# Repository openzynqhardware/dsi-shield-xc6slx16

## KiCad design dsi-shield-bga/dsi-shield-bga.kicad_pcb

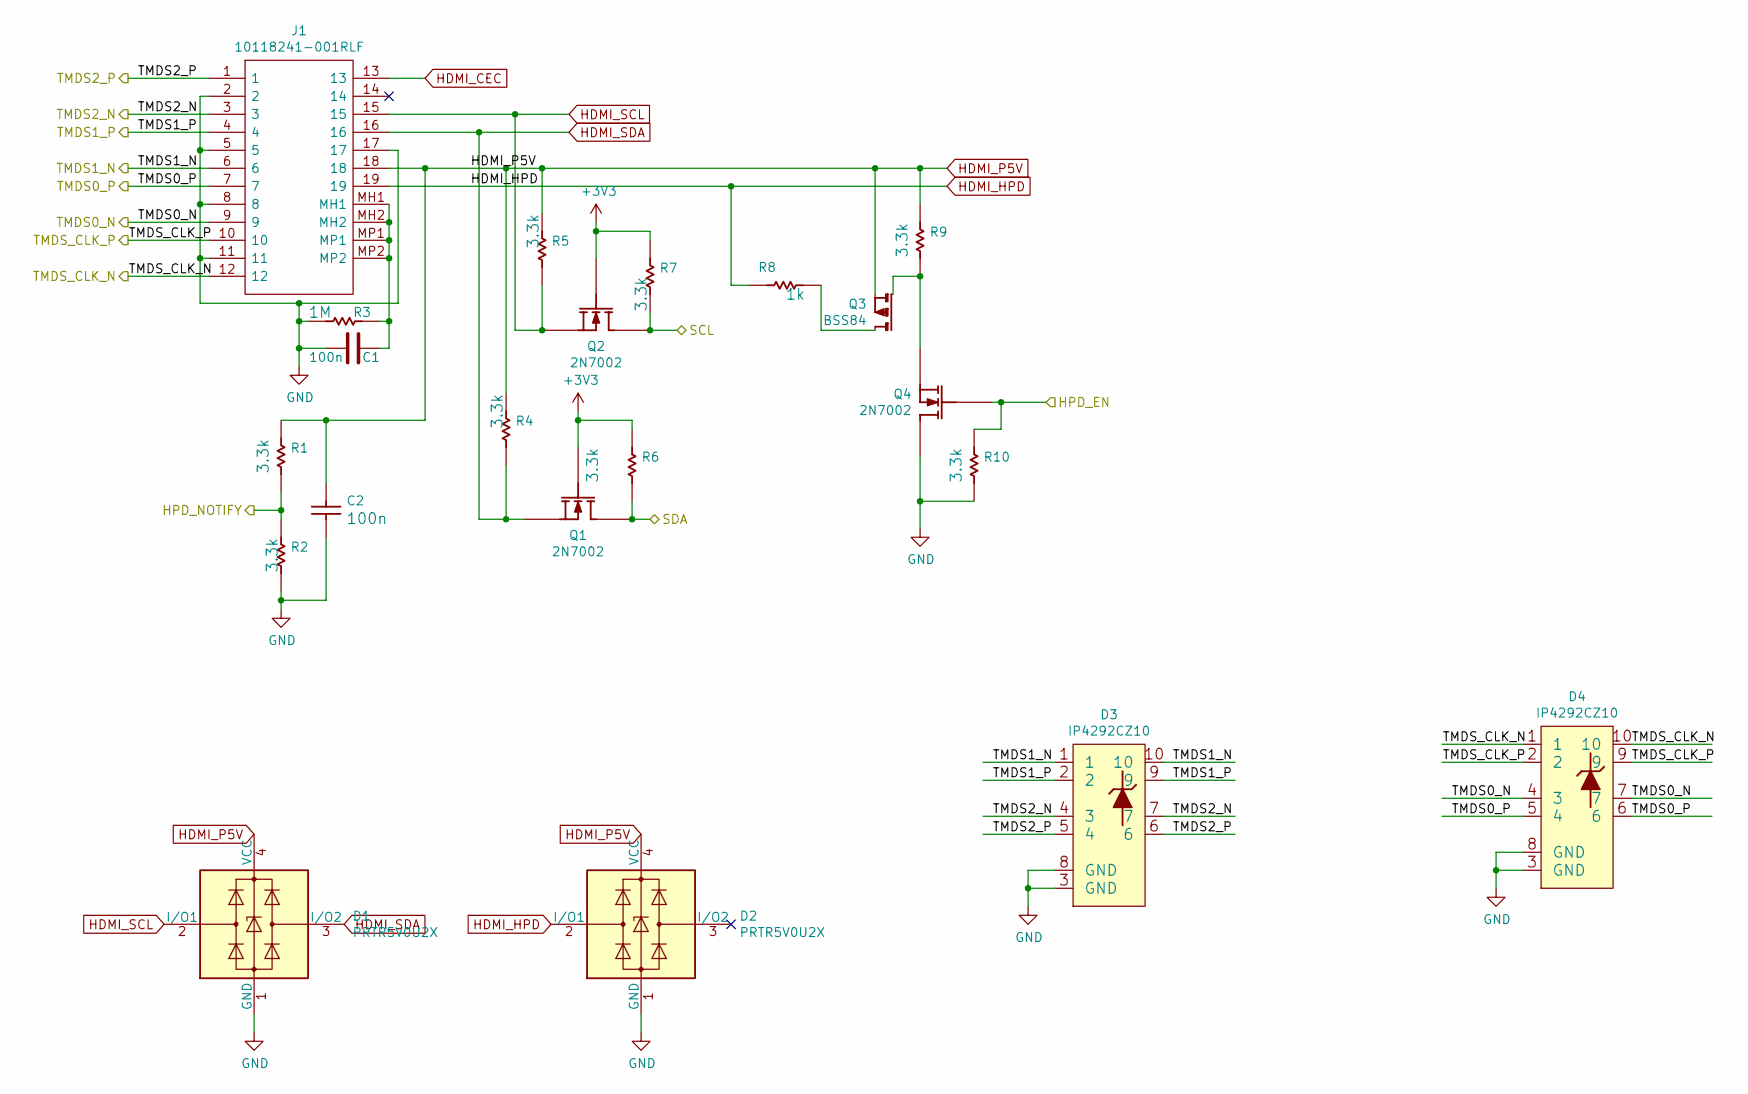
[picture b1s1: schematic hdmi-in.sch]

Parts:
C1, C2: 100n; C_01005_0402Metric
D1, D2: PRTR5V0U2X; SOT-143
D3, D4: IP4292CZ10; SOT1176-1
J1: 10118241-001RLF; 10118241001RLF; Mouser Part Number 649-10118241-001RLF
Q1, Q2, Q4: 2N7002; SOT-23
Q3: Q_BSS84; SOT-23
R1, R2, R4, R5, R6, R7, R9, R10: 3.3k; R_0402_1005Metric
R3: 1M; R_0402_1005Metric
R8: 1k; R_0402_1005Metric

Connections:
/Sheet5F173767/HPD_EN: Q4.1 (G), R10.1; also elsewhere on the board
/Sheet5F173767/HPD_NOTIFY: R1.2, R2.1; also elsewhere on the board
/Sheet5F173767/SCL: Q2.3 (D), R7.2; also elsewhere on the board
/Sheet5F173767/SDA: Q1.3 (D), R6.2; also elsewhere on the board
/Sheet5F173767/TMDS0_N: D4.4 (3), D4.7, J1.9; also elsewhere on the board
/Sheet5F173767/TMDS0_P: D4.5 (4), D4.6, J1.7; also elsewhere on the board
/Sheet5F173767/TMDS1_N: D3.1, D3.10, J1.6; also elsewhere on the board
/Sheet5F173767/TMDS1_P: D3.2, D3.9, J1.4; also elsewhere on the board
/Sheet5F173767/TMDS2_N: D3.4 (3), D3.7, J1.3; also elsewhere on the board
/Sheet5F173767/TMDS2_P: D3.5 (4), D3.6, J1.1; also elsewhere on the board
/Sheet5F173767/TMDS_CLK_N: D4.1, D4.10, J1.12; also elsewhere on the board
/Sheet5F173767/TMDS_CLK_P: D4.2, D4.9, J1.10; also elsewhere on the board
GND: C1.2, C2.2, D1.1 (GND), D2.1 (GND), D3.3 (GND), D3.8 (GND), D4.3 (GND), D4.8 (GND), J1.2, J1.5, J1.8, J1.11, J1.17, Q4.3 (D), R2.2, R3.1, R10.2; also elsewhere on the board
HDMI_CEC: J1.13
HDMI_HPD: D2.2 (I/O1), J1.19, R8.1
HDMI_P5V: C2.1, D1.4 (VCC), D2.4 (VCC), J1.18, Q3.2 (S), R1.1, R4.1, R5.1, R9.1
HDMI_SCL: D1.2 (I/O1), J1.15, Q2.2 (S), R5.2
HDMI_SDA: D1.3 (I/O2), J1.16, Q1.2 (S), R4.2
unnamed: C1.1, J1.MH1, J1.MH2, J1.MP1, J1.MP2, R3.2
unnamed: Q3.1 (G), Q4.2 (S), R9.2
unnamed: Q3.3 (D), R8.2

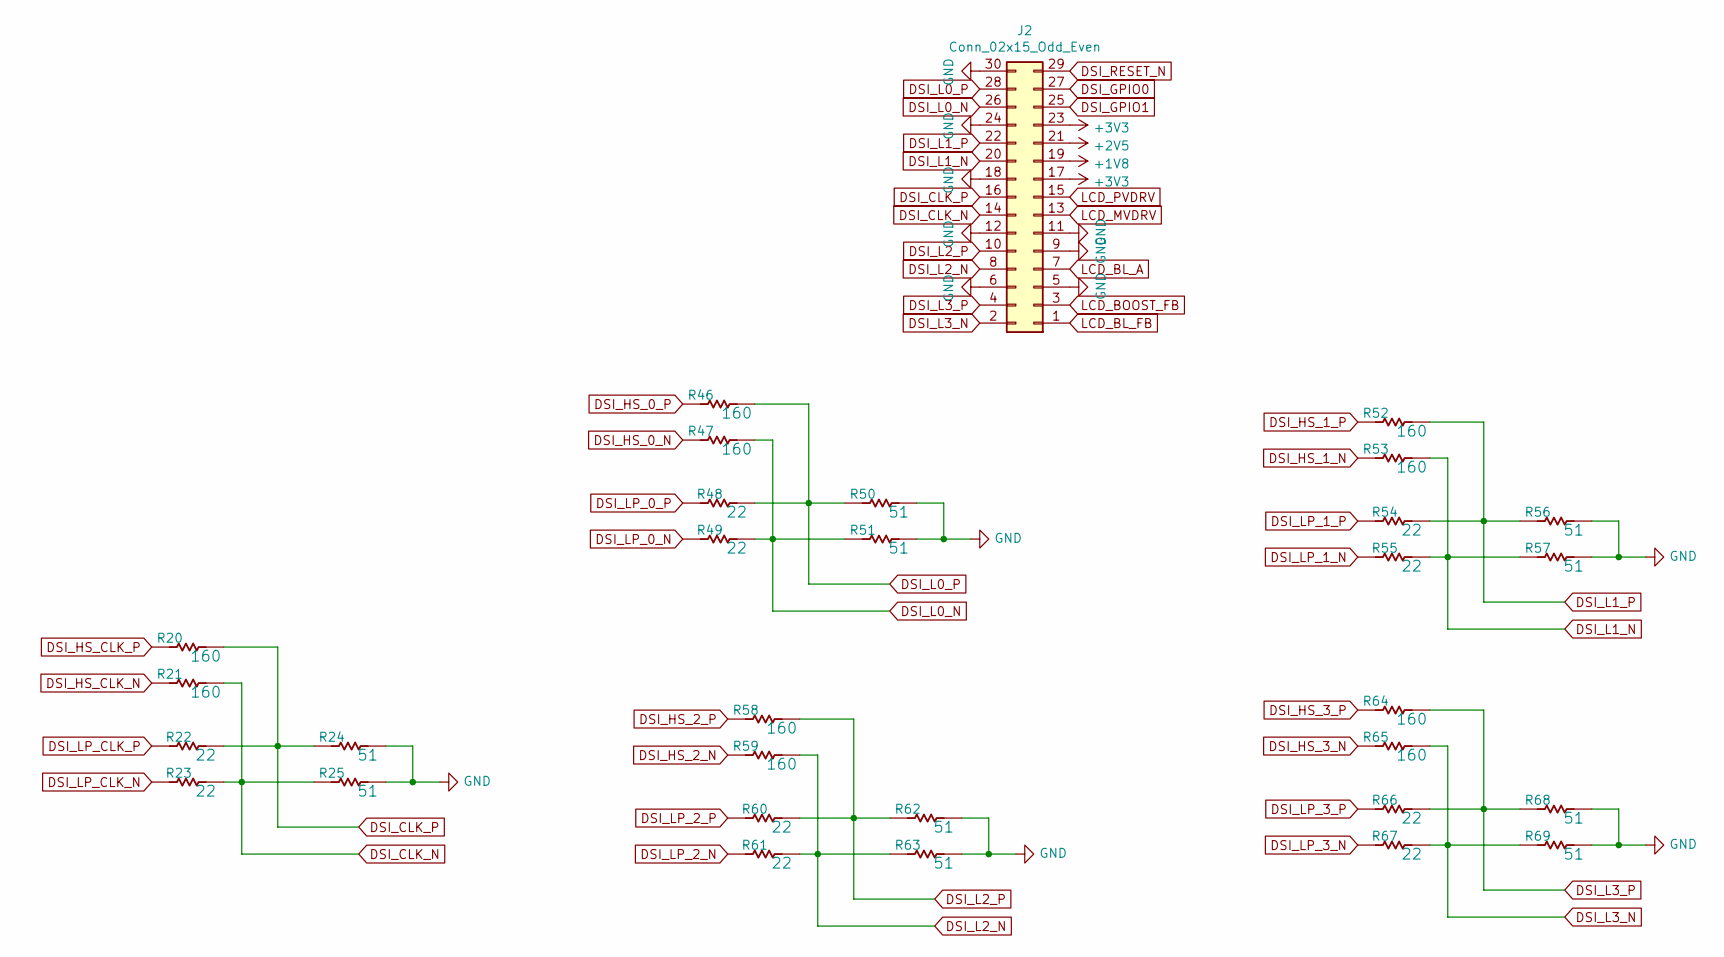
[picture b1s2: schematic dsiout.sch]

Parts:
J2: Conn_02x15_Odd_Even; PinHeader_2x15_P2.54mm_Vertical
R20, R21, R46, R47, R52, R53, R58, R59, R64, R65: 160; R_0402_1005Metric
R22, R23, R48, R49, R54, R55, R60, R61, R66, R67: 22; R_0402_1005Metric
R24, R25, R50, R51, R56, R57, R62, R63, R68, R69: 51; R_0402_1005Metric

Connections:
+1V8: J2.19; also elsewhere on the board
+2V5: J2.21; also elsewhere on the board
DSI_CLK_N: J2.14, R21.2, R23.2, R25.1
DSI_CLK_P: J2.16, R20.2, R22.2, R24.1
DSI_GPIO0: J2.27; also elsewhere on the board
DSI_GPIO1: J2.25; also elsewhere on the board
DSI_HS_0_N: R47.1; also elsewhere on the board
DSI_HS_0_P: R46.1; also elsewhere on the board
DSI_HS_1_N: R53.1; also elsewhere on the board
DSI_HS_1_P: R52.1; also elsewhere on the board
DSI_HS_2_N: R59.1; also elsewhere on the board
DSI_HS_2_P: R58.1; also elsewhere on the board
DSI_HS_3_N: R65.1; also elsewhere on the board
DSI_HS_3_P: R64.1; also elsewhere on the board
DSI_HS_CLK_N: R21.1; also elsewhere on the board
DSI_HS_CLK_P: R20.1; also elsewhere on the board
DSI_L0_N: J2.26, R47.2, R49.2, R51.1
DSI_L0_P: J2.28, R46.2, R48.2, R50.1
DSI_L1_N: J2.20, R53.2, R55.2, R57.1
DSI_L1_P: J2.22, R52.2, R54.2, R56.1
DSI_L2_N: J2.8, R59.2, R61.2, R63.1
DSI_L2_P: J2.10, R58.2, R60.2, R62.1
DSI_L3_N: J2.2, R65.2, R67.2, R69.1
DSI_L3_P: J2.4, R64.2, R66.2, R68.1
DSI_LP_0_N: R49.1; also elsewhere on the board
DSI_LP_0_P: R48.1; also elsewhere on the board
DSI_LP_1_N: R55.1; also elsewhere on the board
DSI_LP_1_P: R54.1; also elsewhere on the board
DSI_LP_2_N: R61.1; also elsewhere on the board
DSI_LP_2_P: R60.1; also elsewhere on the board
DSI_LP_3_N: R67.1; also elsewhere on the board
DSI_LP_3_P: R66.1; also elsewhere on the board
DSI_LP_CLK_N: R23.1; also elsewhere on the board
DSI_LP_CLK_P: R22.1; also elsewhere on the board
DSI_RESET_N: J2.29; also elsewhere on the board
GND: J2.5, J2.6, J2.9, J2.11, J2.12, J2.18, J2.24, J2.30, R24.2, R25.2, R50.2, R51.2, R56.2, R57.2, R62.2, R63.2, R68.2, R69.2; also elsewhere on the board
LCD_BL_A: J2.7; also elsewhere on the board
LCD_BL_FB: J2.1; also elsewhere on the board
LCD_BOOST_FB: J2.3; also elsewhere on the board
LCD_MVDRV: J2.13
LCD_PVDRV: J2.15

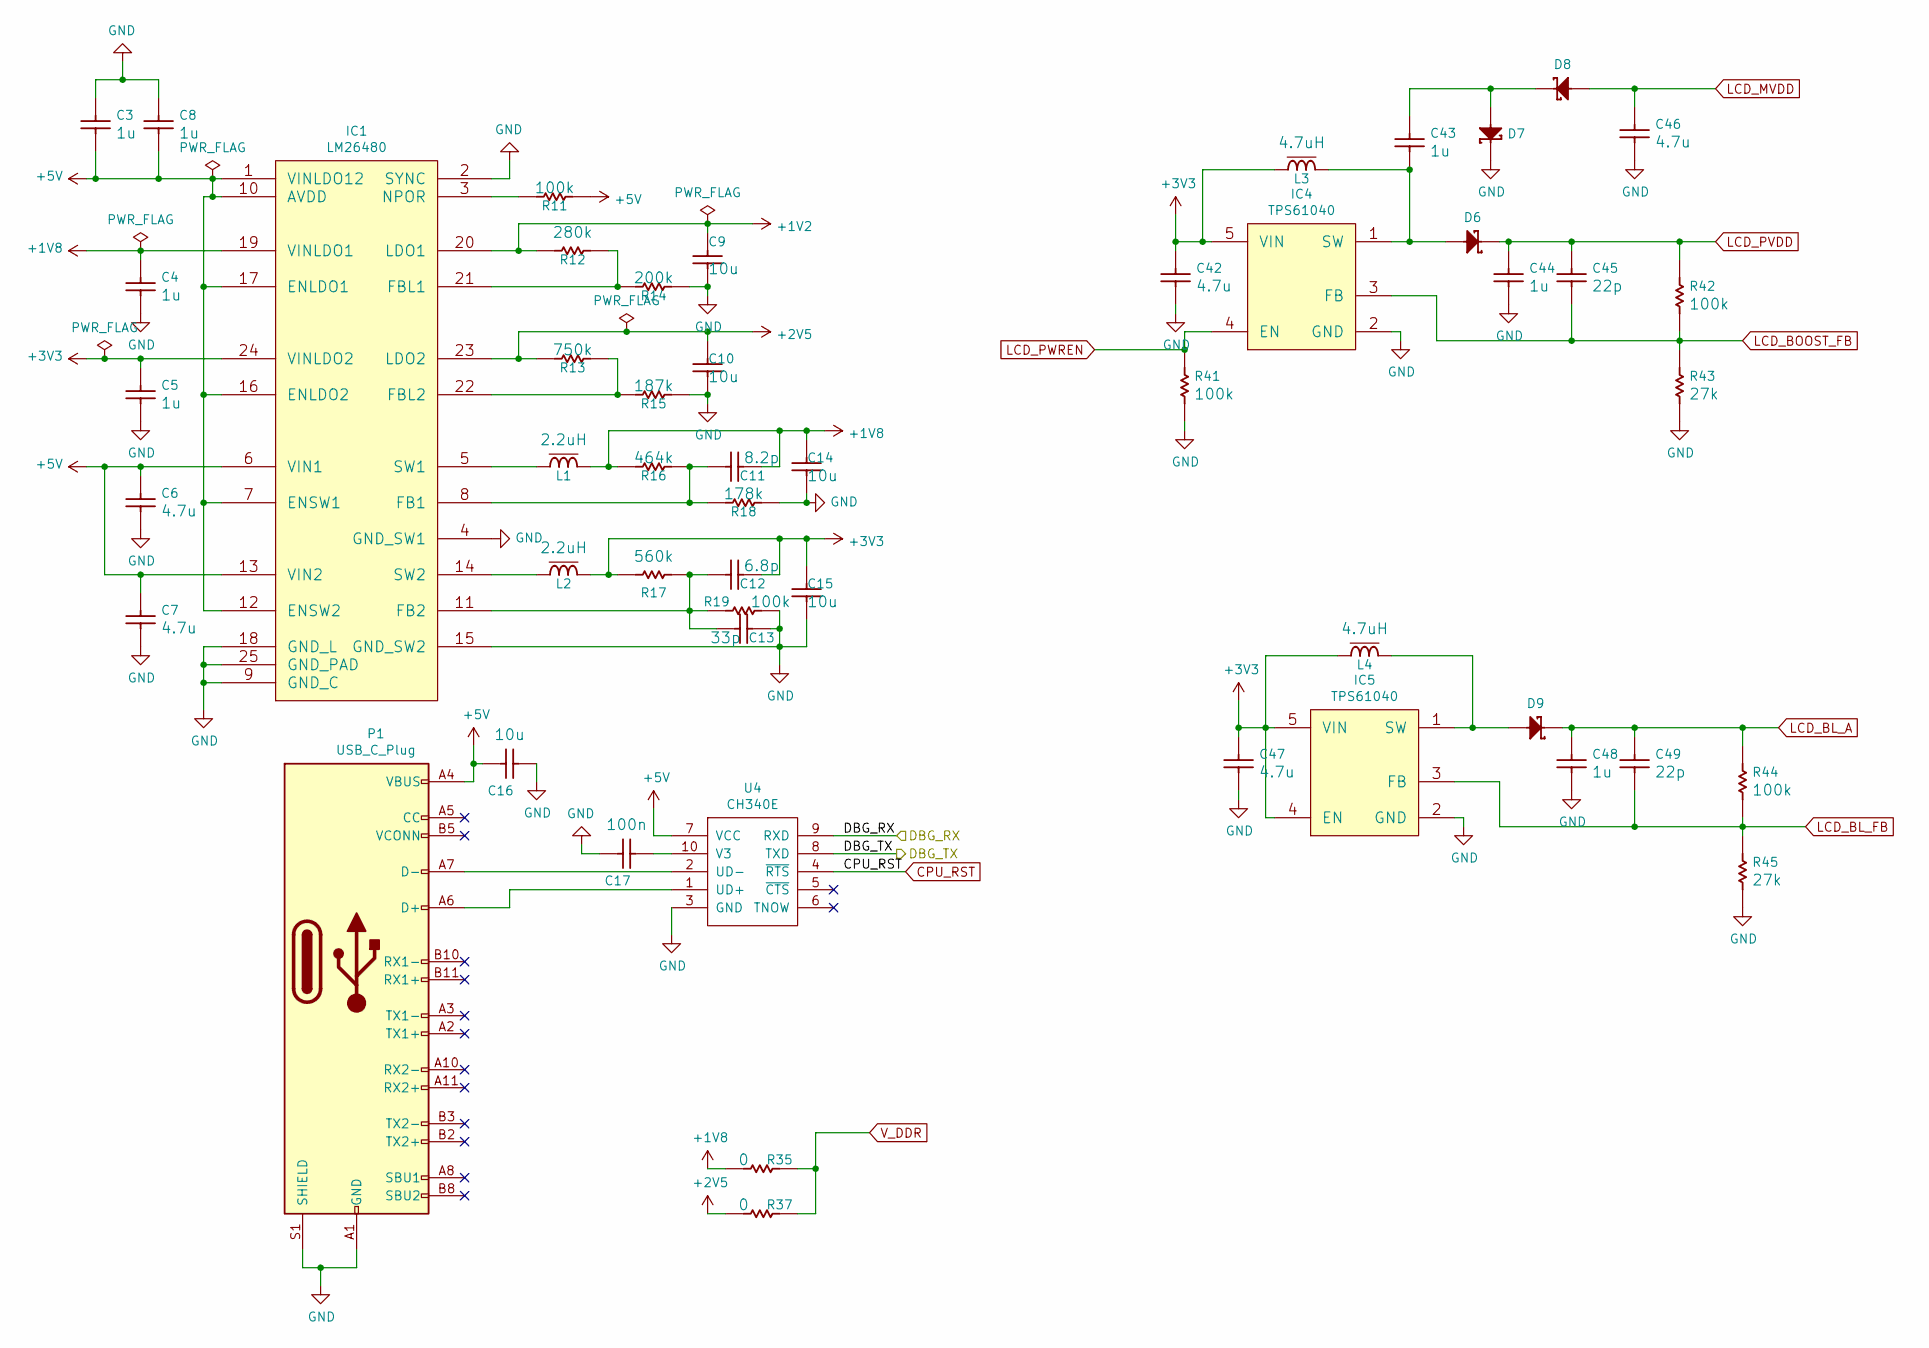
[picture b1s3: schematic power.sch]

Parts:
C3, C4, C5, C8: 1u; C_0603_1608Metric
C6, C7: 4.7u; C_0603_1608Metric
C9, C10, C14, C15, C16: 10u; C_0603_1608Metric
C11: 8.2p; C_0402_1005Metric
C12: 6.8p; C_0402_1005Metric
C13: 33p; C_0402_1005Metric
C17: 100n; C_0402_1005Metric
C42, C46, C47: 4.7u; C_0805_2012Metric
C43, C44, C48: 1u; C_0603_1608Metric_Pad1.05x0.95mm_HandSolder
C45, C49: 22p; C_0402_1005Metric
D6, D7, D8, D9: Diode_Schottky; SOD3715X145N
IC1: LM26480; WQFN-24-1EP_4x4mm_P0.5mm_EP2.6x2.6mm
IC4, IC5: SOT95P275X110-5N
L1, L2: 2.2uH; IND_PANASONIC_ELLVEG
L3, L4: 4.7uH; IND_PANASONIC_ELLVEG
P1: USB_C_Plug; USB_C_Receptacle_Amphenol_12401548E4-2A
R11, R19, R41, R42, R44: 100k; R_0402_1005Metric
R12: 280k; R_0402_1005Metric
R13: 750k; R_0402_1005Metric
R14: 200k; R_0402_1005Metric
R15: 187k; R_0402_1005Metric
R16: 464k; R_0402_1005Metric
R17: 560k; R_0402_1005Metric
R18: 178k; R_0402_1005Metric
R35, R37: 0; R_0402_1005Metric
R43, R45: 27k; R_0402_1005Metric
U4: CH340E; MSOP-10-1EP_3x3mm_P0.5mm_EP1.68x1.88mm_ThermalVias

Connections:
+1V2: C9.1, IC1.20 (LDO1), R12.1; also elsewhere on the board
+1V8: C4.1, C11.2, C14.1, IC1.19 (VINLDO1), L1.2, R16.1, R35.1; also elsewhere on the board
+2V5: C10.1, IC1.23 (LDO2), R13.1, R37.1; also elsewhere on the board
+5V: C3.2, C6.1, C7.1, C8.2, C16.1, IC1.1 (VINLDO12), IC1.6 (VIN1), IC1.7 (ENSW1), IC1.10 (AVDD), IC1.12 (ENSW2), IC1.13 (VIN2), IC1.16 (ENLDO2), IC1.17 (ENLDO1), P1.A4 (VBUS), P1.A9 (VBUS), P1.B4 (VBUS), P1.B9 (VBUS), R11.2, U4.7 (VCC)
/Sheet5F12EB4F/DBG_RX: U4.9 (RXD); also elsewhere on the board
/Sheet5F173767/DBG_RX: U4.8 (TXD); also elsewhere on the board
CPU_RST: U4.4 (~RTS~); also elsewhere on the board
GND: C3.1, C4.2, C5.2, C6.2, C7.2, C8.1, C9.2, C10.2, C13.2, C14.2, C15.2, C16.2, C17.1, C42.2, C44.2, C46.2, C47.2, C48.2, D7.1 (C), IC1.2 (SYNC), IC1.4 (GND_SW1), IC1.9 (GND_C), IC1.15 (GND_SW2), IC1.18 (GND_L), IC1.25 (GND_PAD), IC4.2 (GND), IC5.2 (GND), P1.A1 (GND), P1.A12 (GND), P1.B1 (GND), P1.B12 (GND), P1.S1 (SHIELD), R14.2, R15.2, R18.2, R19.2, R41.2, R43.2, R45.2, U4.3 (GND); also elsewhere on the board
LCD_BL_A: C48.1, C49.1, D9.1 (C), R44.1; also elsewhere on the board
LCD_BL_FB: C49.2, IC5.3 (FB), R44.2, R45.1; also elsewhere on the board
LCD_BOOST_FB: C45.2, IC4.3 (FB), R42.2, R43.1; also elsewhere on the board
LCD_MVDD: C46.1, D8.2 (A)
LCD_PVDD: C44.1, C45.1, D6.1 (C), R42.1
LCD_PWREN: IC4.4 (EN), R41.1; also elsewhere on the board
unnamed: C11.1, IC1.8 (FB1), R16.2, R18.1
unnamed: C12.1, C13.1, IC1.11 (FB2), R17.2, R19.1
unnamed: C17.2, U4.10 (V3)
unnamed: C43.1, D7.2 (A), D8.1 (C)
unnamed: C43.2, D6.2 (A), IC4.1 (SW), L3.2
unnamed: D9.2 (A), IC5.1 (SW), L4.2
unnamed: IC1.3 (NPOR), R11.1
unnamed: IC1.5 (SW1), L1.1
unnamed: IC1.14 (SW2), L2.1
unnamed: IC1.21 (FBL1), R12.2, R14.1
unnamed: IC1.22 (FBL2), R13.2, R15.1
unnamed: P1.A6 (D+), U4.1 (UD+)
unnamed: P1.A7 (D-), U4.2 (UD-)
V_DDR: R35.2, R37.2; also elsewhere on the board

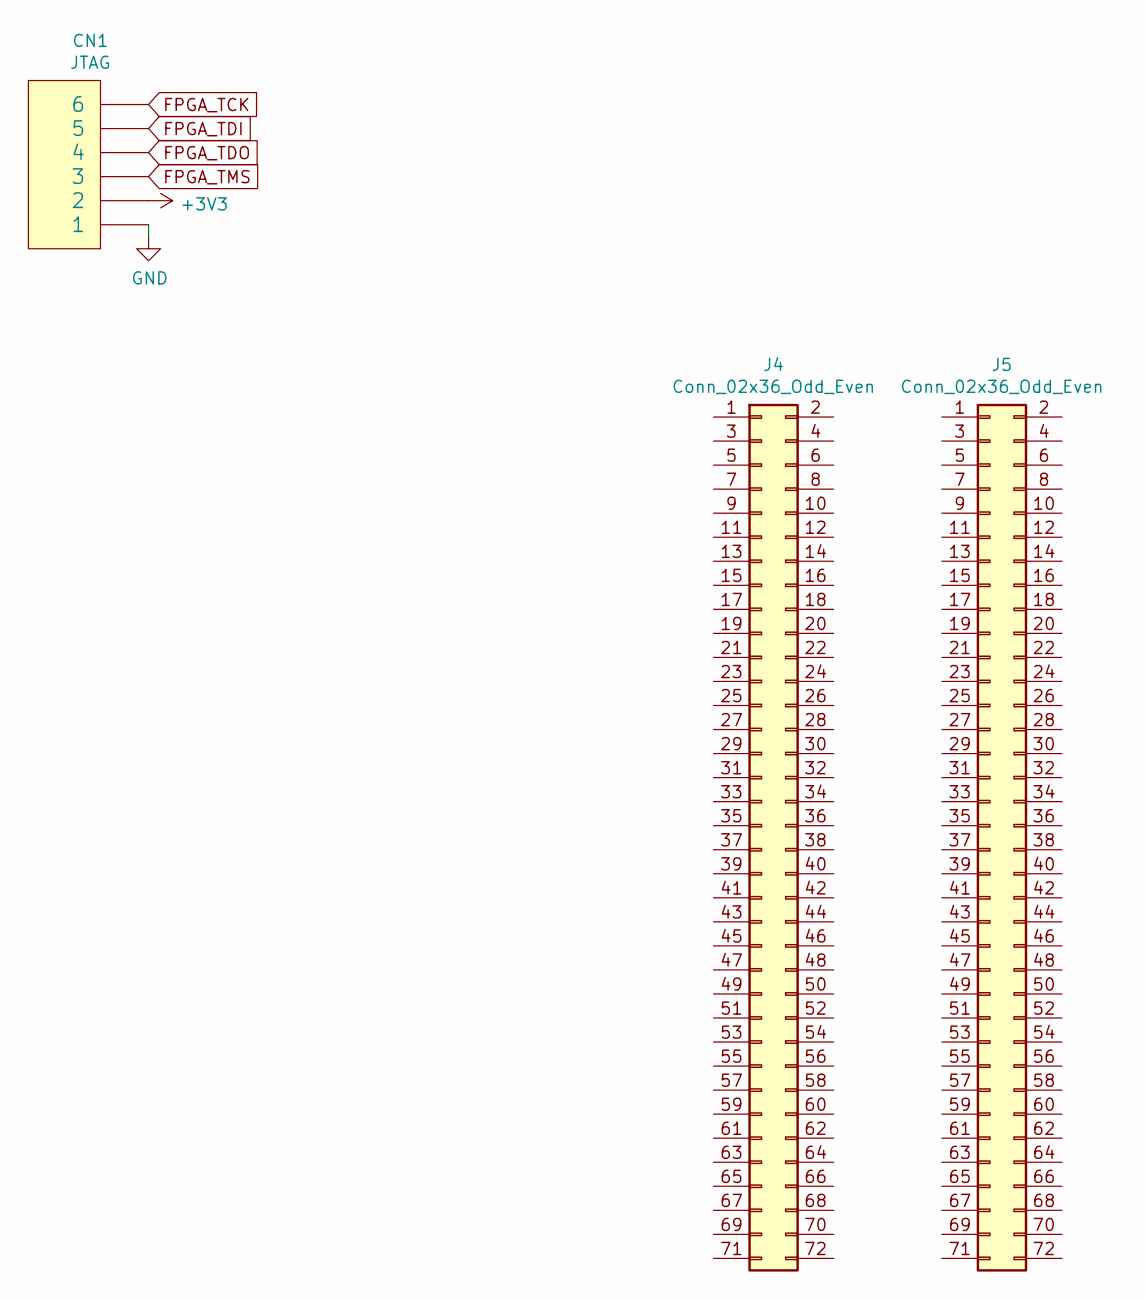
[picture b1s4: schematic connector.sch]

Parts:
CN1: Header_6; Header 6x1 8.5mm
J4, J5: Conn_02x36_Odd_Even; PinSocket_2x36_P2.54mm_Vertical

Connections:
FPGA_TCK: CN1.6; also elsewhere on the board
FPGA_TDI: CN1.5; also elsewhere on the board
FPGA_TDO: CN1.4; also elsewhere on the board
FPGA_TMS: CN1.3; also elsewhere on the board
GND: CN1.1; also elsewhere on the board

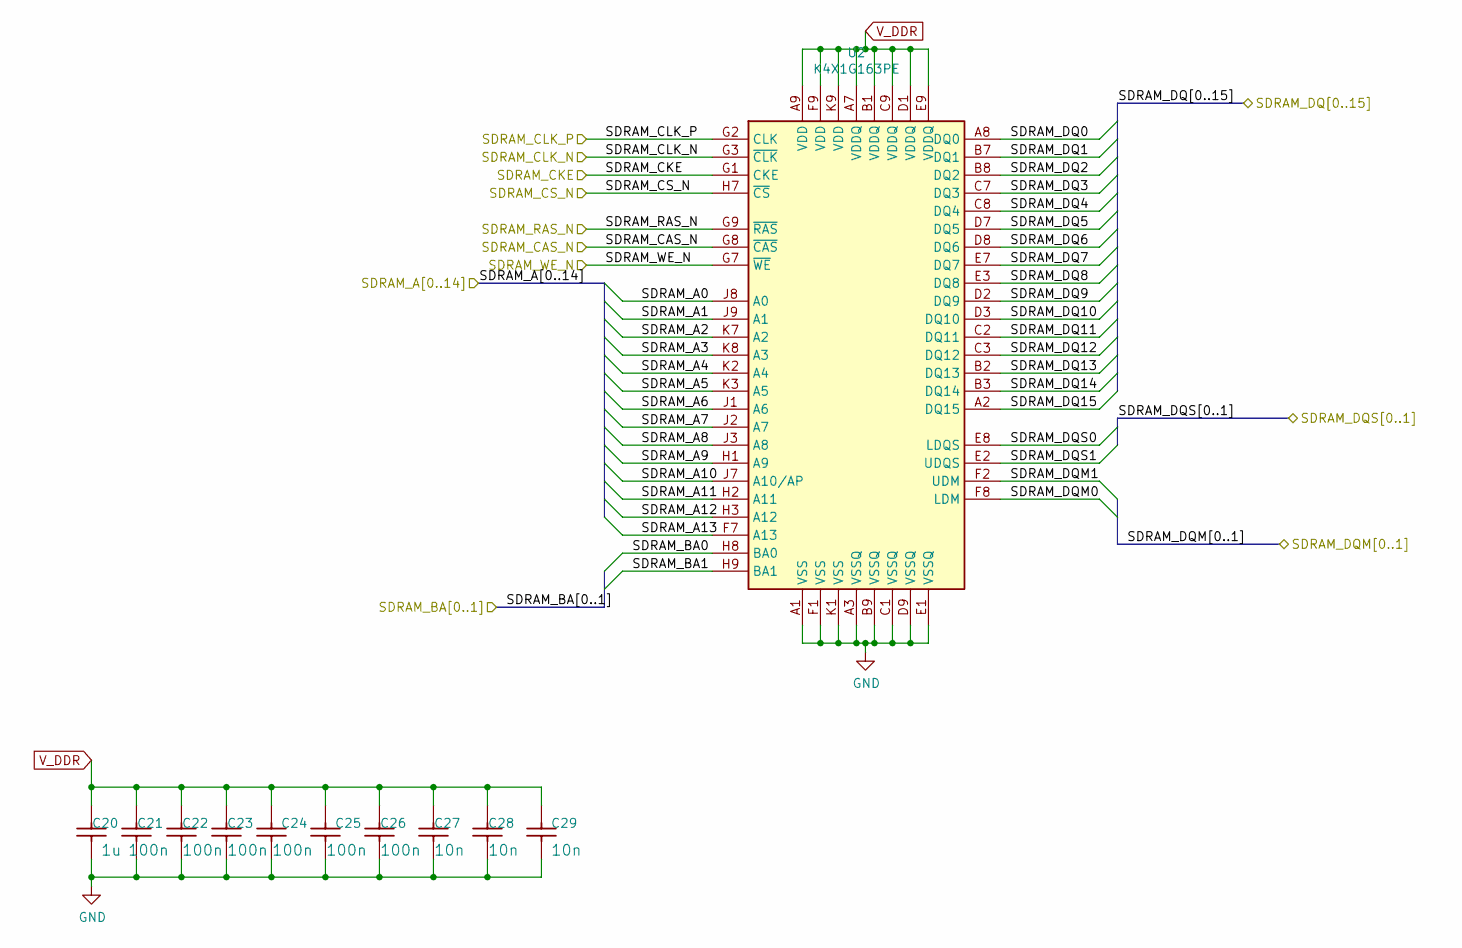
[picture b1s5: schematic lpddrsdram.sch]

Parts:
C20: 1u; C_0402_1005Metric
C21, C22, C23, C24, C25, C26: 100n; C_0402_1005Metric
C27, C28, C29: 10n; C_0402_1005Metric
U2: K4X1G163PE; FBGA60-6X10

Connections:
/Sheet5F173767/SDRAM_A0: U2.J8 (A0); also elsewhere on the board
/Sheet5F173767/SDRAM_A1: U2.J9 (A1); also elsewhere on the board
/Sheet5F173767/SDRAM_A2: U2.K7 (A2); also elsewhere on the board
/Sheet5F173767/SDRAM_A3: U2.K8 (A3); also elsewhere on the board
/Sheet5F173767/SDRAM_A4: U2.K2 (A4); also elsewhere on the board
/Sheet5F173767/SDRAM_A5: U2.K3 (A5); also elsewhere on the board
/Sheet5F173767/SDRAM_A6: U2.J1 (A6); also elsewhere on the board
/Sheet5F173767/SDRAM_A7: U2.J2 (A7); also elsewhere on the board
/Sheet5F173767/SDRAM_A8: U2.J3 (A8); also elsewhere on the board
/Sheet5F173767/SDRAM_A9: U2.H1 (A9); also elsewhere on the board
/Sheet5F173767/SDRAM_A10: U2.J7 (A10/AP); also elsewhere on the board
/Sheet5F173767/SDRAM_A11: U2.H2 (A11); also elsewhere on the board
/Sheet5F173767/SDRAM_A12: U2.H3 (A12); also elsewhere on the board
/Sheet5F173767/SDRAM_A13: U2.F7 (A13); also elsewhere on the board
/Sheet5F173767/SDRAM_BA0: U2.H8 (BA0); also elsewhere on the board
/Sheet5F173767/SDRAM_BA1: U2.H9 (BA1); also elsewhere on the board
/Sheet5F173767/SDRAM_CAS_N: U2.G8 (~CAS); also elsewhere on the board
/Sheet5F173767/SDRAM_CKE: U2.G1 (CKE); also elsewhere on the board
/Sheet5F173767/SDRAM_CLK_N: U2.G3 (~CLK); also elsewhere on the board
/Sheet5F173767/SDRAM_CLK_P: U2.G2 (CLK); also elsewhere on the board
/Sheet5F173767/SDRAM_CS_N: U2.H7 (~CS); also elsewhere on the board
/Sheet5F173767/SDRAM_DQ0: U2.A8 (DQ0); also elsewhere on the board
/Sheet5F173767/SDRAM_DQ1: U2.B7 (DQ1); also elsewhere on the board
/Sheet5F173767/SDRAM_DQ2: U2.B8 (DQ2); also elsewhere on the board
/Sheet5F173767/SDRAM_DQ3: U2.C7 (DQ3); also elsewhere on the board
/Sheet5F173767/SDRAM_DQ4: U2.C8 (DQ4); also elsewhere on the board
/Sheet5F173767/SDRAM_DQ5: U2.D7 (DQ5); also elsewhere on the board
/Sheet5F173767/SDRAM_DQ6: U2.D8 (DQ6); also elsewhere on the board
/Sheet5F173767/SDRAM_DQ7: U2.E7 (DQ7); also elsewhere on the board
/Sheet5F173767/SDRAM_DQ8: U2.E3 (DQ8); also elsewhere on the board
/Sheet5F173767/SDRAM_DQ9: U2.D2 (DQ9); also elsewhere on the board
/Sheet5F173767/SDRAM_DQ10: U2.D3 (DQ10); also elsewhere on the board
/Sheet5F173767/SDRAM_DQ11: U2.C2 (DQ11); also elsewhere on the board
/Sheet5F173767/SDRAM_DQ12: U2.C3 (DQ12); also elsewhere on the board
/Sheet5F173767/SDRAM_DQ13: U2.B2 (DQ13); also elsewhere on the board
/Sheet5F173767/SDRAM_DQ14: U2.B3 (DQ14); also elsewhere on the board
/Sheet5F173767/SDRAM_DQ15: U2.A2 (DQ15); also elsewhere on the board
/Sheet5F173767/SDRAM_DQM0: U2.F8 (LDM); also elsewhere on the board
/Sheet5F173767/SDRAM_DQM1: U2.F2 (UDM); also elsewhere on the board
/Sheet5F173767/SDRAM_DQS0: U2.E8 (LDQS); also elsewhere on the board
/Sheet5F173767/SDRAM_DQS1: U2.E2 (UDQS); also elsewhere on the board
/Sheet5F173767/SDRAM_RAS_N: U2.G9 (~RAS); also elsewhere on the board
/Sheet5F173767/SDRAM_WE_N: U2.G7 (~WE); also elsewhere on the board
GND: C20.2, C21.2, C22.2, C23.2, C24.2, C25.2, C26.2, C27.2, C28.2, C29.2, U2.A1 (VSS), U2.A3 (VSSQ), U2.B9 (VSSQ), U2.C1 (VSSQ), U2.D9 (VSSQ), U2.E1 (VSSQ), U2.F1 (VSS), U2.K1 (VSS); also elsewhere on the board
V_DDR: C20.1, C21.1, C22.1, C23.1, C24.1, C25.1, C26.1, C27.1, C28.1, C29.1, U2.A7 (VDDQ), U2.A9 (VDD), U2.B1 (VDDQ), U2.C9 (VDDQ), U2.D1 (VDDQ), U2.E9 (VDDQ), U2.F9 (VDD), U2.K9 (VDD); also elsewhere on the board

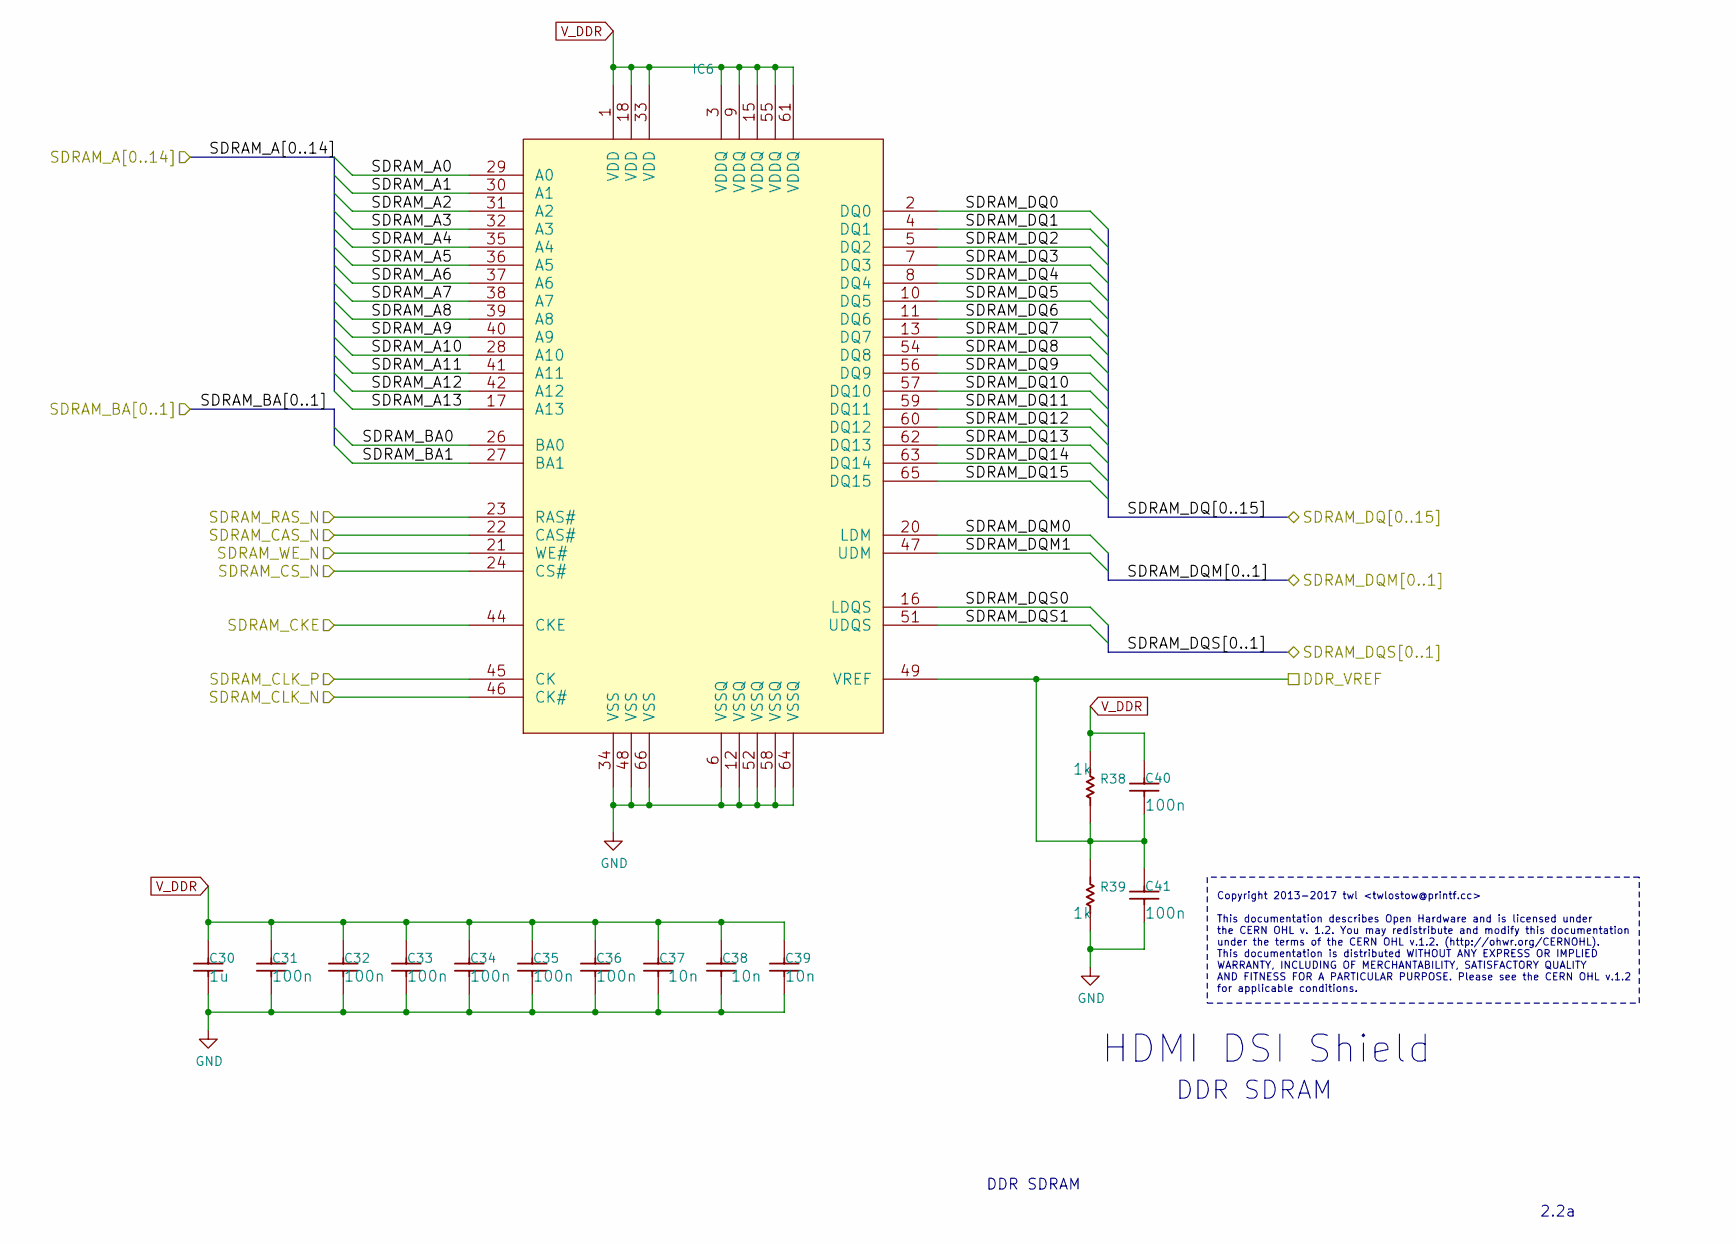
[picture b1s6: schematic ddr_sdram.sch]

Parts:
C30: 1u; C_0402_1005Metric
C31, C32, C33, C34, C35, C36, C40, C41: 100n; C_0402_1005Metric
C37, C38, C39: 10n; C_0402_1005Metric
IC6: MT46V64M16P-5B_F; TSOP66
R38, R39: 1k; R_0402_1005Metric

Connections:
/Sheet5F173767/DDR_VREF: C40.2, C41.1, IC6.49 (VREF), R38.2, R39.1; also elsewhere on the board
/Sheet5F173767/SDRAM_A0: IC6.29 (A0); also elsewhere on the board
/Sheet5F173767/SDRAM_A1: IC6.30 (A1); also elsewhere on the board
/Sheet5F173767/SDRAM_A2: IC6.31 (A2); also elsewhere on the board
/Sheet5F173767/SDRAM_A3: IC6.32 (A3); also elsewhere on the board
/Sheet5F173767/SDRAM_A4: IC6.35 (A4); also elsewhere on the board
/Sheet5F173767/SDRAM_A5: IC6.36 (A5); also elsewhere on the board
/Sheet5F173767/SDRAM_A6: IC6.37 (A6); also elsewhere on the board
/Sheet5F173767/SDRAM_A7: IC6.38 (A7); also elsewhere on the board
/Sheet5F173767/SDRAM_A8: IC6.39 (A8); also elsewhere on the board
/Sheet5F173767/SDRAM_A9: IC6.40 (A9); also elsewhere on the board
/Sheet5F173767/SDRAM_A10: IC6.28 (A10); also elsewhere on the board
/Sheet5F173767/SDRAM_A11: IC6.41 (A11); also elsewhere on the board
/Sheet5F173767/SDRAM_A12: IC6.42 (A12); also elsewhere on the board
/Sheet5F173767/SDRAM_A13: IC6.17 (A13); also elsewhere on the board
/Sheet5F173767/SDRAM_BA0: IC6.26 (BA0); also elsewhere on the board
/Sheet5F173767/SDRAM_BA1: IC6.27 (BA1); also elsewhere on the board
/Sheet5F173767/SDRAM_CAS_N: IC6.22 (CAS#); also elsewhere on the board
/Sheet5F173767/SDRAM_CKE: IC6.44 (CKE); also elsewhere on the board
/Sheet5F173767/SDRAM_CLK_N: IC6.46 (CK#); also elsewhere on the board
/Sheet5F173767/SDRAM_CLK_P: IC6.45 (CK); also elsewhere on the board
/Sheet5F173767/SDRAM_CS_N: IC6.24 (CS#); also elsewhere on the board
/Sheet5F173767/SDRAM_DQ0: IC6.2 (DQ0); also elsewhere on the board
/Sheet5F173767/SDRAM_DQ1: IC6.4 (DQ1); also elsewhere on the board
/Sheet5F173767/SDRAM_DQ2: IC6.5 (DQ2); also elsewhere on the board
/Sheet5F173767/SDRAM_DQ3: IC6.7 (DQ3); also elsewhere on the board
/Sheet5F173767/SDRAM_DQ4: IC6.8 (DQ4); also elsewhere on the board
/Sheet5F173767/SDRAM_DQ5: IC6.10 (DQ5); also elsewhere on the board
/Sheet5F173767/SDRAM_DQ6: IC6.11 (DQ6); also elsewhere on the board
/Sheet5F173767/SDRAM_DQ7: IC6.13 (DQ7); also elsewhere on the board
/Sheet5F173767/SDRAM_DQ8: IC6.54 (DQ8); also elsewhere on the board
/Sheet5F173767/SDRAM_DQ9: IC6.56 (DQ9); also elsewhere on the board
/Sheet5F173767/SDRAM_DQ10: IC6.57 (DQ10); also elsewhere on the board
/Sheet5F173767/SDRAM_DQ11: IC6.59 (DQ11); also elsewhere on the board
/Sheet5F173767/SDRAM_DQ12: IC6.60 (DQ12); also elsewhere on the board
/Sheet5F173767/SDRAM_DQ13: IC6.62 (DQ13); also elsewhere on the board
/Sheet5F173767/SDRAM_DQ14: IC6.63 (DQ14); also elsewhere on the board
/Sheet5F173767/SDRAM_DQ15: IC6.65 (DQ15); also elsewhere on the board
/Sheet5F173767/SDRAM_DQM0: IC6.20 (LDM); also elsewhere on the board
/Sheet5F173767/SDRAM_DQM1: IC6.47 (UDM); also elsewhere on the board
/Sheet5F173767/SDRAM_DQS0: IC6.16 (LDQS); also elsewhere on the board
/Sheet5F173767/SDRAM_DQS1: IC6.51 (UDQS); also elsewhere on the board
/Sheet5F173767/SDRAM_RAS_N: IC6.23 (RAS#); also elsewhere on the board
/Sheet5F173767/SDRAM_WE_N: IC6.21 (WE#); also elsewhere on the board
GND: C30.2, C31.2, C32.2, C33.2, C34.2, C35.2, C36.2, C37.2, C38.2, C39.2, C41.2, IC6.6 (VSSQ), IC6.12 (VSSQ), IC6.34 (VSS), IC6.48 (VSS), IC6.52 (VSSQ), IC6.58 (VSSQ), IC6.64 (VSSQ), IC6.66 (VSS), R39.2; also elsewhere on the board
V_DDR: C30.1, C31.1, C32.1, C33.1, C34.1, C35.1, C36.1, C37.1, C38.1, C39.1, C40.1, IC6.1 (VDD), IC6.3 (VDDQ), IC6.9 (VDDQ), IC6.15 (VDDQ), IC6.18 (VDD), IC6.33 (VDD), IC6.55 (VDDQ), IC6.61 (VDDQ), R38.1; also elsewhere on the board

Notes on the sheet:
Copyright 2013-2017 twl <twlostow@printf.cc> This documentation describes Open Hardware and is licensed under the CERN OHL v. 1.2. You may redistribute and modify this documentation under the terms of the CERN OHL v.1.2. (http://ohwr.org/CERNOHL). This documentation is distributed WITHOUT ANY EXPRE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
HDMI DSI Shield
DDR SDRAM
2.2a
